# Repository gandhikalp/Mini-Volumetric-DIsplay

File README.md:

# Volumetric Display Prototype

A swept-volume volumetric display built from scratch using a 
scotch yoke mechanism, custom SMT PCB, and Waveshare ESP32-S3-Matrix.

**Status:** Electronics and PCB tested ✅ | Mechanical assembly pending 🔄

> ⚠️ **Note:** This is an active prototype project. Thus, Hardware files and firmware are subject to rapid iterations.
---

## What This Is

A proof-of-concept volumetric display similar in basic principle to the 
Voxon VX1. An 8×8 RGB LED matrix sweeps vertically at ~16Hz 
using a scotch yoke mechanism, creating a 3D persistence-of-vision 
image visible from multiple angles.\
It is highly inspired from [Matthew Lim's video](https://youtu.be/KgT20tHpk1g?si=lmqNyyaOBYBv9zQp) on youtube about mini volumetric display.

---

## Hardware

| Component | Details |
|---|---|
| Microcontroller | Waveshare ESP32-S3-Matrix (8×8 RGB LED matrix) |
| Custom PCB | 2-layer SMT, designed in Fusion 360, fabricated by Lion Circuits |
| Motor | GA12-N20 6V 1000RPM DC motor |
| Motor driver | DRV8838DSGR (on the PCB) |
| Position sensing | Dual ITR-9606 opto interrupters |
| Mechanism | Scotch yoke |
| PCB size | 27.5mm × 40mm |

---

## Firmware Architecture 

Core 0 (real-time):\
→ Motor PWM control via DRV8838\
→ Dual opto interrupt handling\
→ Slice timing calculation

Core 1 (non-critical):\
→ WiFi connection\
→ OTA wireless firmware updates\
→ Web debug dashboard

---

## Current Progress

- [DONE] Custom PCB designed, fabricated, assembled
- [DONE] Motor control verified (3 speeds via PWM)
- [DONE] Dual opto interrupter timing verified
- [DONE] Dual-core firmware with WiFi debug dashboard
- [DONE] OTA wireless firmware updates
- [PENDING] Desgining cad v_2
- [PENDING] Mechanical assembly
- [PENDING] Volumetric slice display firmware

---

## Repository Structure

```text
├── hardware/
│   ├── pcb/               # Gerber Files, BOM, schematic, PCB photos
│   └── cad/        
│       ├── failed_design/     # First design + notes on why it failed
│       └── current_design/    # Current redesigned mechanism
├── firmware/              # Arduino IDE sketches
├── build_log/                  # Build log, images
└── references/            # Inspiration and related work
```
---

## PCB

Custom 2-layer controller board handling:
- USB-C power input with proper CC resistor negotiation(5.1k ohms resistors)
- DRV8838DSGR motor driver (1.8A capable)
- Dual opto interrupter interface circuits
- 7-pin interface to ESP32 board
- Status LED

Fabricated by Lion Circuits, India.

---

## Why **Scotch Yoke** Mechanism?

Unlike rack-and-pinion (used in Matthew Lim's build) and slider crank mechanism (which also used for converting circular motion into linear reciprocating motion), 
Scotch Yoke produces Simple Harmonic Motion:
- Screen dwells longer at extremes → better brightness distribution
- No backlash at direction reversal
- Smoother reversal → lower vibration
- Mathematically clean position from sin(angle)

---

## Build Log

See [build_log.md](build_log/build_log.md)

---

## Related Work

- [Matthew Lim's mini volumetric display](https://youtu.be/KgT20tHpk1g?si=lmqNyyaOBYBv9zQp)
- [Voxon Photonics VX1/VX2](https://voxon.co)

---

## Author

Gandhi Kalp — 2nd year B.Tech Civil Engineering, IIT ISM Dhanbad  
Interests: Robotics, Embedded Systems, IoT, ML and Automation

Check my [LinkedIn](https://www.linkedin.com/in/gandhikalpniravkumar/?skipRedirect=true)

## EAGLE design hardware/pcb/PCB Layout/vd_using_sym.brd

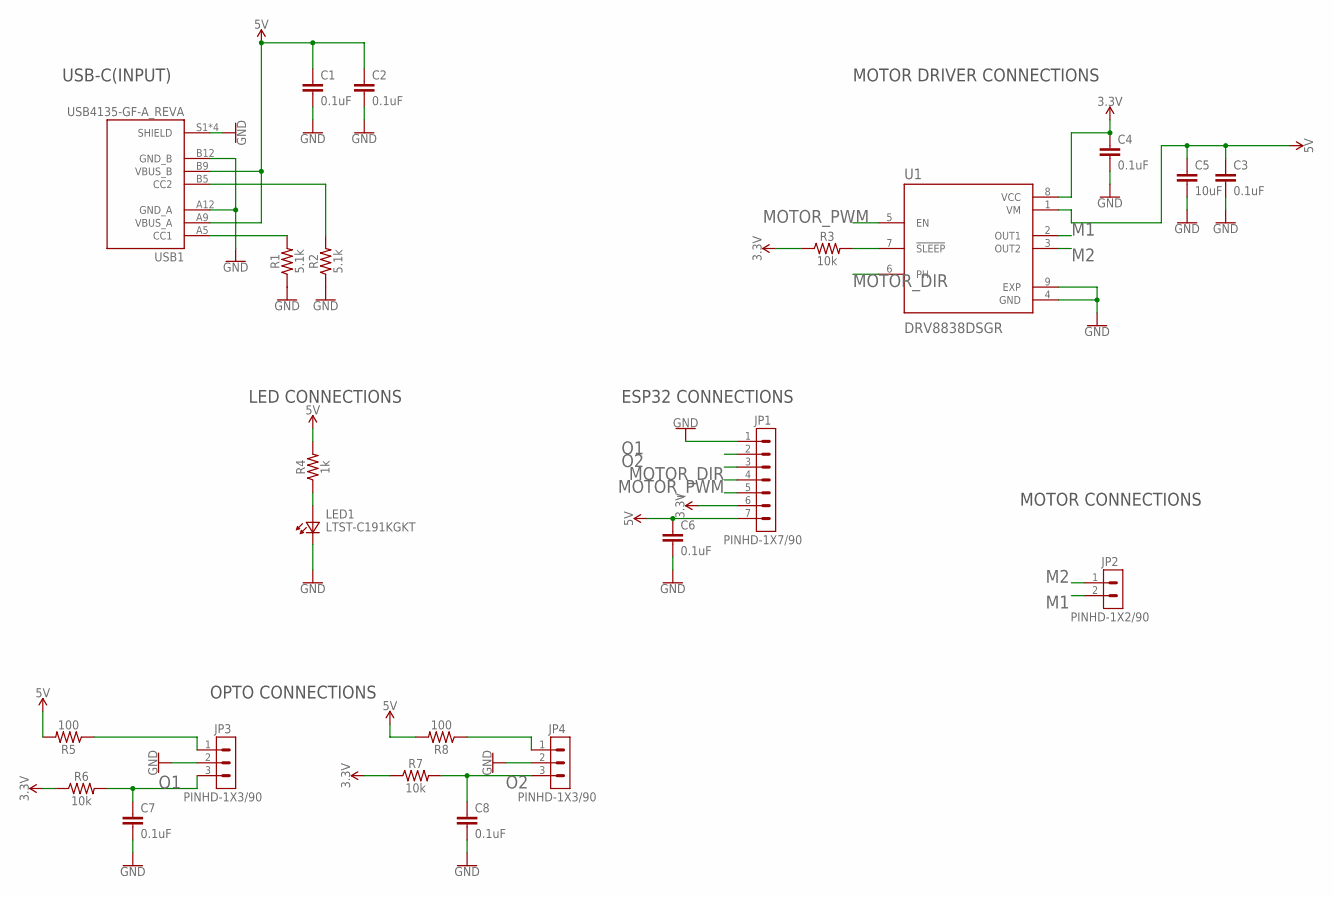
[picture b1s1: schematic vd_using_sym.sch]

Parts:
C1, C2, C3, C4, C6, C7, C8: 0.1uF; 0402-TIGHT
C5: 10uF; 0805
JP1: PINHD-1X7/90; 1X07_90
JP2: PINHD-1X2/90; 1X02_90
JP3, JP4: PINHD-1X3/90; 1X03_90
LED1: LTST-C191KGKT; 0603
R1, R2: 5.1k; 0402-TIGHT
R3, R6, R7: 10k; 0402-TIGHT
R4: 1k; 0402-TIGHT
R5, R8: 100; 0402-TIGHT
U1: DRV8838DSGR; SON50P200X200X80-9N
USB1: USB4135-GF-A_REVA; GCT_USB4135-GF-A_REVA

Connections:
3.3V: C4.1, JP1.6, R3.1, R6.1, R7.1, U1.8 (VCC)
5V: C1.1, C2.1, C3.1, C5.1, C6.1, JP1.7, R4.2, R5.2, R8.2, U1.1 (VM), USB1.A9 (VBUS_A), USB1.B9 (VBUS_B)
GND: C1.2, C2.2, C3.2, C4.2, C5.2, C6.2, C7.2, C8.2, JP1.1, JP3.2, JP4.2, LED1.1 (K2), R1.1, R2.1, U1.4 (GND), U1.9 (EXP), USB1.A12 (GND_A), USB1.B12 (GND_B), USB1.S1 (SHIELD), USB1.S2 (SHIELD), USB1.S3 (SHIELD), USB1.S4 (SHIELD)
M1: JP2.2, U1.2 (OUT1)
M2: JP2.1, U1.3 (OUT2)
MOTOR_DIR: JP1.4, U1.6 (PH)
MOTOR_PWM: JP1.5, U1.5 (EN)
unnamed: R1.2, USB1.A5 (CC1)
unnamed: R2.2, USB1.B5 (CC2)
unnamed: R3.2, U1.7 (!SLEEP)
unnamed: LED1.2 (A2), R4.1
unnamed: JP3.1, R5.1
unnamed: JP4.1, R8.1
O1: C7.1, JP1.2, JP3.3, R6.2
O2: C8.1, JP1.3, JP4.3, R7.2

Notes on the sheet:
USB-C(INPUT)
MOTOR DRIVER CONNECTIONS
ESP32 CONNECTIONS
LED CONNECTIONS
MOTOR CONNECTIONS
OPTO CONNECTIONS

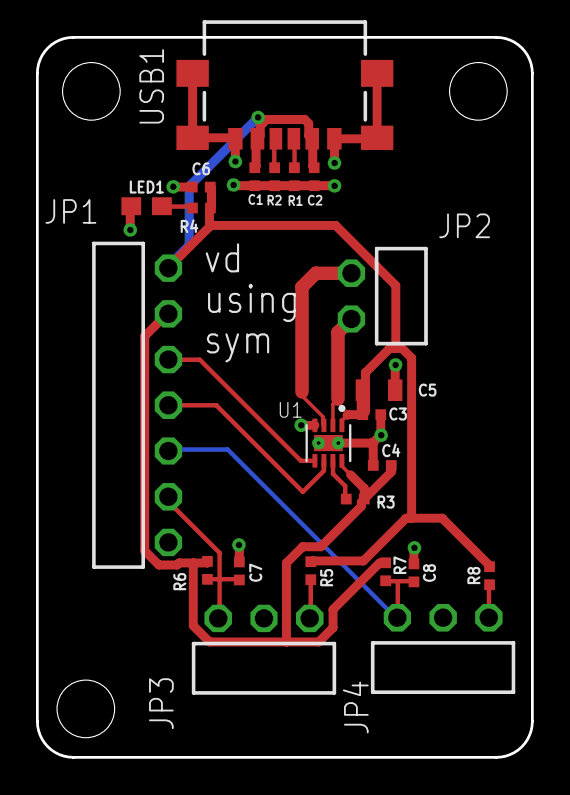
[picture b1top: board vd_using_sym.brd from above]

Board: 2 copper layers, 27.5 x 40.0 mm, 23 parts (0 on the bottom side), 15 nets.

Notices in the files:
parts and their libraries:
SparkFun-Resistors: Licensing: Creative Commons ShareAlike 4.0 International - https://creativecommons.org/licenses/by-sa/4.0
